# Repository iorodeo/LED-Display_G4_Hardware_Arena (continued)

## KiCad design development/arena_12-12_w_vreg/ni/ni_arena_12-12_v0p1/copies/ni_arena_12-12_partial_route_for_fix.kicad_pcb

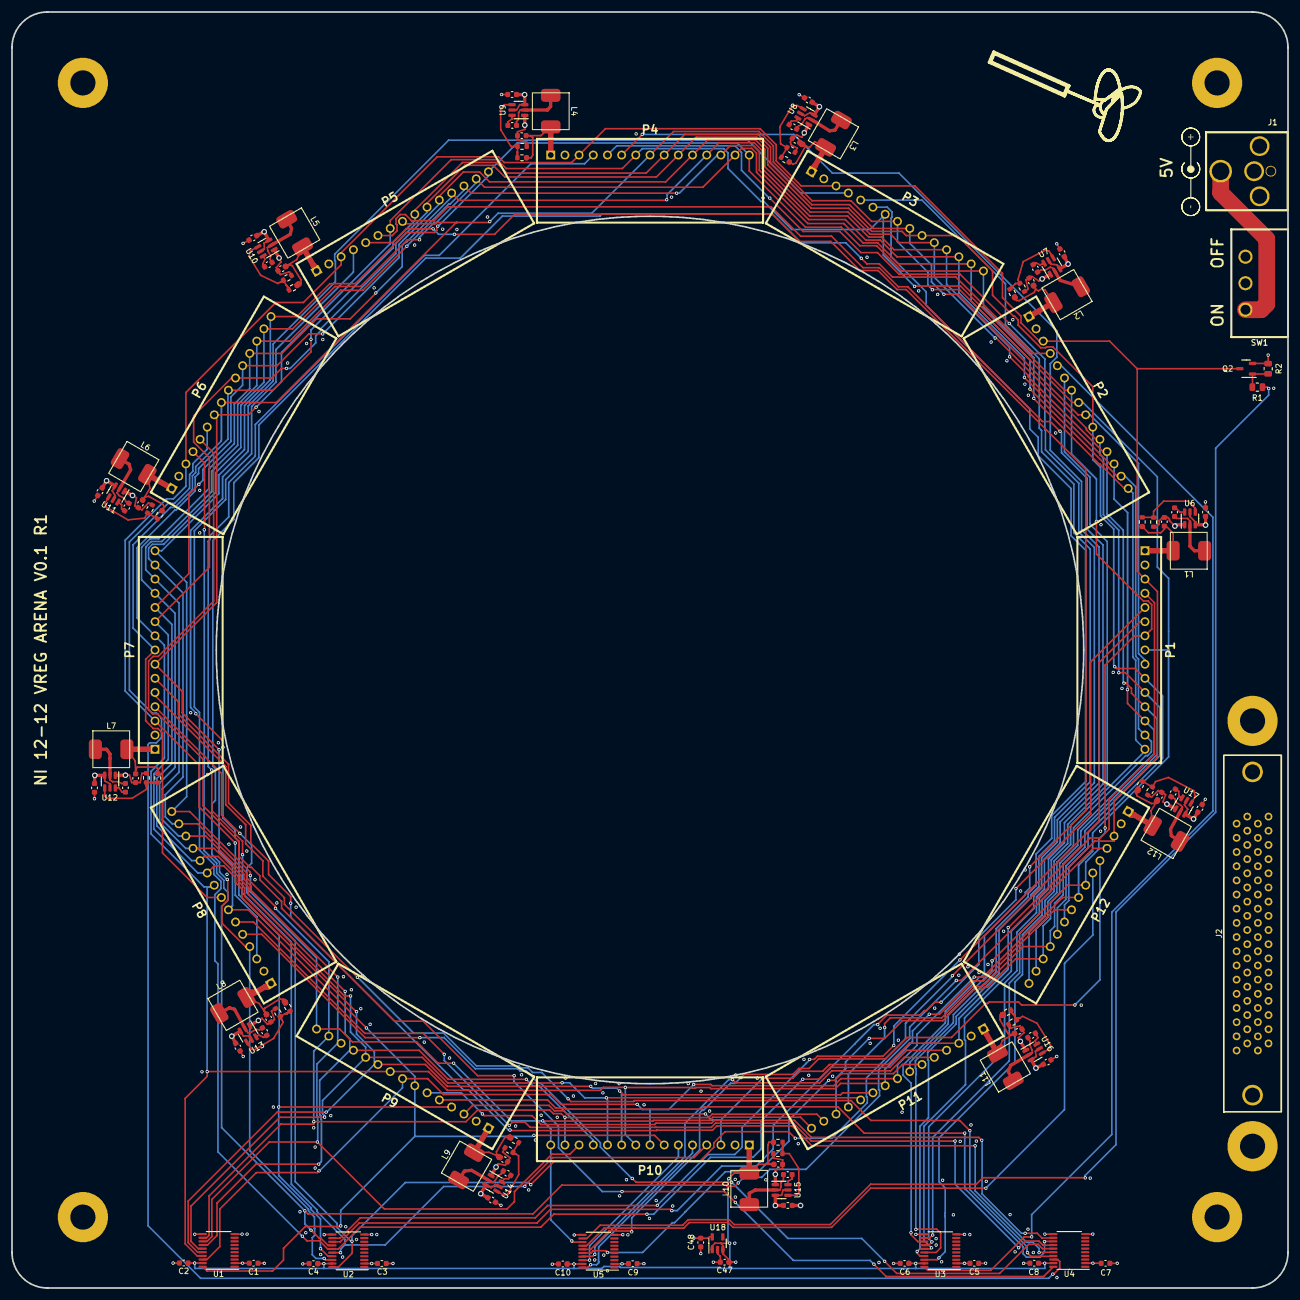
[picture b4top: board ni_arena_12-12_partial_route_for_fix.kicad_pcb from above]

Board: 6 copper layers, 228.6 x 228.6 mm, 126 parts (0 on the bottom side), 134 nets.

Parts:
C1, C2, C3, C4, C5, C6, C7, C8, C9, C10: 0.1uF; C_0603_1608Metric
C11, C14, C17, C20, C23, C26, C29, C32, C35, C38, C41, C44, C47, C48: 10uF; C_0603_1608Metric
C12, C15, C18, C21, C24, C27, C30, C33, C36, C39, C42, C45: 100nF; C_0603_1608Metric
C13, C16, C19, C22, C25, C28, C31, C34, C37, C40, C43, C46: 22uF; C_0603_1608Metric
H1, H2, H3, H4, H5, H6: MountingHole_Pad; MountingHole_4.5mm_Pad
J1: Barrel_Jack; DCJACK_2PIN_HIGHCURRENT
J2: NI_TE_68pos; TE_CONN_DSUB_VERT_68
L1, L2, L3, L4, L5, L6, L7, L8, L9, L10, L11, L12: 3.3uH; CYA0650_3P3UH
P1, P2, P3, P4, P5, P6, P7, P8, P9, P10, P11, P12: CONN15; HEADER_TOP
Q2: MOSFET_NCHAN; SOT-23-3
R1: 200; R_0805_2012Metric
R2: 20k; R_0805_2012Metric
R3, R5, R7, R9, R11, R13, R15, R17, R19, R21, R23, R25: 56.2k; R_0603_1608Metric
R4, R6, R8, R10, R12, R14, R16, R18, R20, R22, R24, R26: 10k; R_0603_1608Metric
SW1: SW_SPDT; slide_switch
U1, U2, U3, U4, U5: TXB0108PW; TSSOP-20_4.4x6.5mm_P0.65mm
U6, U7, U8, U9, U10, U11, U12, U13, U14, U15, U16, U17: TPS564201DDC; SOT-23-6
U18: AP2112K-3.3; SOT-23-5

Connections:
+3.3V: C1.1, C3.1, C5.1, C7.1, C9.1, C48.1, U1.2 (VCCA), U1.10 (OE), U2.2 (VCCA), U2.10 (OE), U3.2 (VCCA), U3.10 (OE), U4.2 (VCCA), U4.10 (OE), U5.2 (VCCA), U5.10 (OE), U18.5 (VOUT)
/Level Shifters/PAN3V.CS_00: J2.35, U1.1 (A1)
/Level Shifters/PAN3V.CS_01: J2.36, U1.3 (A2)
/Level Shifters/PAN3V.CS_02: J2.37, U1.4 (A3)
/Level Shifters/PAN3V.CS_03: J2.38, U1.5 (A4)
/Level Shifters/PAN3V.CS_04: J2.39, U1.6 (A5)
/Level Shifters/PAN3V.CS_05: J2.40, U1.7 (A6)
/Level Shifters/PAN3V.CS_06: J2.41, U1.8 (A7)
/Level Shifters/PAN3V.CS_07: J2.42, U1.9 (A8)
/Level Shifters/PAN3V.EXT_INT: J2.68, U5.8 (A7)
/Level Shifters/PAN3V.MISO_00: J2.50, U2.9 (A8)
/Level Shifters/PAN3V.MISO_01: J2.52, U3.3 (A2)
/Level Shifters/PAN3V.MISO_02: J2.54, U3.5 (A4)
/Level Shifters/PAN3V.MISO_03: J2.56, U3.7 (A6)
/Level Shifters/PAN3V.MISO_04: J2.58, U3.9 (A8)
/Level Shifters/PAN3V.MISO_05: J2.60, U4.3 (A2)
/Level Shifters/PAN3V.MISO_06: J2.62, U4.5 (A4)
/Level Shifters/PAN3V.MISO_07: J2.63, U4.7 (A6)
/Level Shifters/PAN3V.MISO_08: J2.64, U4.9 (A8)
/Level Shifters/PAN3V.MISO_09: J2.65, U5.3 (A2)
/Level Shifters/PAN3V.MISO_10: J2.66, U5.5 (A4)
/Level Shifters/PAN3V.MISO_11: J2.67, U5.7 (A6)
/Level Shifters/PAN3V.MOSI_00: J2.49, U2.8 (A7)
/Level Shifters/PAN3V.MOSI_01: J2.51, U3.1 (A1)
/Level Shifters/PAN3V.MOSI_02: J2.53, U3.4 (A3)
/Level Shifters/PAN3V.MOSI_03: J2.55, U3.6 (A5)
/Level Shifters/PAN3V.MOSI_04: J2.57, U3.8 (A7)
/Level Shifters/PAN3V.MOSI_05: J2.59, U4.1 (A1)
/Level Shifters/PAN3V.MOSI_06: J2.61, U4.4 (A3)
/Level Shifters/PAN3V.MOSI_07: J2.29, U4.6 (A5)
/Level Shifters/PAN3V.MOSI_08: J2.30, U4.8 (A7)
/Level Shifters/PAN3V.MOSI_09: J2.31, U5.1 (A1)
/Level Shifters/PAN3V.MOSI_10: J2.32, U5.4 (A3)
/Level Shifters/PAN3V.MOSI_11: J2.33, U5.6 (A5)
/Level Shifters/PAN3V.RESET: J2.34, U5.9 (A8)
/Level Shifters/PAN3V.SCK_00: J2.43, U2.1 (A1)
/Level Shifters/PAN3V.SCK_01: J2.44, U2.3 (A2)
/Level Shifters/PAN3V.SCK_02: J2.45, U2.4 (A3)
/Level Shifters/PAN3V.SCK_03: J2.46, U2.5 (A4)
/Level Shifters/PAN3V.SCK_04: J2.47, U2.6 (A5)
/Level Shifters/PAN3V.SCK_05: J2.48, U2.7 (A6)
/Level Shifters/PAN5V.CS_00: P1.7, P2.7, P3.7, P4.7, P5.7, P6.7, P7.7, P8.7, P9.7, P10.7, P11.7, P12.7, U1.20 (B1)
/Level Shifters/PAN5V.CS_01: P1.8, P2.8, P3.8, P4.8, P5.8, P6.8, P7.8, P8.8, P9.8, P10.8, P11.8, P12.8, U1.18 (B2)
/Level Shifters/PAN5V.CS_02: P1.9, P2.9, P3.9, P4.9, P5.9, P6.9, P7.9, P8.9, P9.9, P10.9, P11.9, P12.9, U1.17 (B3)
/Level Shifters/PAN5V.CS_03: P1.10, P2.10, P3.10, P4.10, P5.10, P6.10, P7.10, P8.10, P9.10, P10.10, P11.10, P12.10, U1.16 (B4)
/Level Shifters/PAN5V.CS_04: P1.11, P2.11, P3.11, P4.11, P5.11, P6.11, P7.11, P8.11, P9.11, P10.11, P11.11, P12.11, U1.15 (B5)
/Level Shifters/PAN5V.CS_05: P1.12, P2.12, P3.12, P4.12, P5.12, P6.12, P7.12, P8.12, P9.12, P10.12, P11.12, P12.12, U1.14 (B6)
/Level Shifters/PAN5V.CS_06: P1.13, P2.13, P3.13, P4.13, P5.13, P6.13, P7.13, P8.13, P9.13, P10.13, P11.13, P12.13, U1.13 (B7)
/Level Shifters/PAN5V.CS_07: P1.14, P2.14, P3.14, P4.14, P5.14, P6.14, P7.14, P8.14, P9.14, P10.14, P11.14, P12.14, U1.12 (B8)
/Level Shifters/PAN5V.EXT_INT: P1.15, P2.15, P3.15, P4.15, P5.15, P6.15, P7.15, P8.15, P9.15, P10.15, P11.15, P12.15, U5.13 (B7)
/Level Shifters/PAN5V.MISO_00: P1.6, U2.12 (B8)
/Level Shifters/PAN5V.MISO_01: P2.6, U3.18 (B2)
/Level Shifters/PAN5V.MISO_02: P3.6, U3.16 (B4)
/Level Shifters/PAN5V.MISO_03: P4.6, U3.14 (B6)
/Level Shifters/PAN5V.MISO_04: P5.6, U3.12 (B8)
/Level Shifters/PAN5V.MISO_05: P6.6, U4.18 (B2)
/Level Shifters/PAN5V.MISO_06: P7.6, U4.16 (B4)
/Level Shifters/PAN5V.MISO_07: P8.6, U4.14 (B6)
/Level Shifters/PAN5V.MISO_08: P9.6, U4.12 (B8)
/Level Shifters/PAN5V.MISO_09: P10.6, U5.18 (B2)
/Level Shifters/PAN5V.MISO_10: P11.6, U5.16 (B4)
/Level Shifters/PAN5V.MISO_11: P12.6, U5.14 (B6)
/Level Shifters/PAN5V.MOSI_00: P1.5, U2.13 (B7)
/Level Shifters/PAN5V.MOSI_01: P2.5, U3.20 (B1)
/Level Shifters/PAN5V.MOSI_02: P3.5, U3.17 (B3)
/Level Shifters/PAN5V.MOSI_03: P4.5, U3.15 (B5)
/Level Shifters/PAN5V.MOSI_04: P5.5, U3.13 (B7)
/Level Shifters/PAN5V.MOSI_05: P6.5, U4.20 (B1)
/Level Shifters/PAN5V.MOSI_06: P7.5, U4.17 (B3)
/Level Shifters/PAN5V.MOSI_07: P8.5, U4.15 (B5)
/Level Shifters/PAN5V.MOSI_08: P9.5, U4.13 (B7)
/Level Shifters/PAN5V.MOSI_09: P10.5, U5.20 (B1)
/Level Shifters/PAN5V.MOSI_10: P11.5, U5.17 (B3)
/Level Shifters/PAN5V.MOSI_11: P12.5, U5.15 (B5)
/Level Shifters/PAN5V.RESET: R1.2, U5.12 (B8)
/Level Shifters/PAN5V.SCK_00: P1.4, P7.4, U2.20 (B1)
/Level Shifters/PAN5V.SCK_01: P2.4, P8.4, U2.18 (B2)
/Level Shifters/PAN5V.SCK_02: P3.4, P9.4, U2.17 (B3)
/Level Shifters/PAN5V.SCK_03: P4.4, P10.4, U2.16 (B4)
/Level Shifters/PAN5V.SCK_04: P5.4, P11.4, U2.15 (B5)
/Level Shifters/PAN5V.SCK_05: P6.4, P12.4, U2.14 (B6)
/Level Shifters/POW.5V_HDR_1: C13.2, L1.2, P1.1, R3.1
/Level Shifters/POW.5V_HDR_2: C16.2, L2.2, P2.1, R5.1
/Level Shifters/POW.5V_HDR_3: C19.2, L3.2, P3.1, R7.1
/Level Shifters/POW.5V_HDR_4: C22.2, L4.2, P4.1, R9.1
/Level Shifters/POW.5V_HDR_5: C25.2, L5.2, P5.1, R11.1
/Level Shifters/POW.5V_HDR_6: C28.2, L6.2, P6.1, R13.1
/Level Shifters/POW.5V_HDR_7: C31.2, L7.2, P7.1, R15.1
/Level Shifters/POW.5V_HDR_8: C34.2, L8.2, P8.1, R17.1
/Level Shifters/POW.5V_HDR_9: C37.2, L9.2, P9.1, R19.1
/Level Shifters/POW.5V_HDR_10: C2.1, C4.1, C6.1, C8.1, C10.1, C40.2, C47.1, L10.2, P10.1, R21.1, U1.19 (VCCB), U2.19 (VCCB), U3.19 (VCCB), U4.19 (VCCB), U5.19 (VCCB), U18.1 (VIN), U18.3 (EN)
/Level Shifters/POW.5V_HDR_11: C43.2, L11.2, P11.1, R23.1
/Level Shifters/POW.5V_HDR_12: C46.2, L12.2, P12.1, R25.1
/Panel Headers/RESET: P1.3, P2.3, P3.3, P4.3, P5.3, P6.3, P7.3, P8.3, P9.3, P10.3, P11.3, P12.3, Q2.3 (D)
/Power & Voltage Regulators/SW_VCC: J1.1, SW1.1 (A)
GND: C1.2, C2.2, C3.2, C4.2, C5.2, C6.2, C7.2, C8.2, C9.2, C10.2, C11.2, C13.1, C14.2, C16.1, C17.2, C19.1, C20.2, C22.1, C23.2, C25.1, C26.2, C28.1, C29.2, C31.1, C32.2, C34.1, C35.2, C37.1, C38.2, C40.1, C41.2, C43.1, C44.2, C46.1, C47.2, C48.2, H1.1, H2.1, H3.1, H4.1, H5.1, H6.1, J1.2, J2.1, J2.2, J2.3, J2.69 (GND), J2.70 (GND), P1.2, P2.2, P3.2, P4.2, P5.2, P6.2, P7.2, P8.2, P9.2, P10.2, P11.2, P12.2, Q2.2 (S), R2.1, R4.2, R6.2, R8.2, R10.2, R12.2, R14.2, R16.2, R18.2, R20.2, R22.2, R24.2, R26.2, SW1.3 (C), U1.11 (GND), U2.11 (GND), U3.11 (GND), U4.11 (GND), U5.11 (GND), U6.1 (GND), U7.1 (GND), U8.1 (GND), U9.1 (GND), U10.1 (GND), U11.1 (GND), U12.1 (GND), U13.1 (GND), U14.1 (GND), U15.1 (GND), U16.1 (GND), U17.1 (GND), U18.2 (GND)
unnamed: Q2.1 (G), R1.1, R2.2
unnamed: C12.2, L1.1, U6.2 (SW)
unnamed: C12.1, U6.6 (VBST)
unnamed: R3.2, R4.1, U6.4 (VFB)
unnamed: C15.2, L2.1, U7.2 (SW)
unnamed: C15.1, U7.6 (VBST)
unnamed: R5.2, R6.1, U7.4 (VFB)
unnamed: C18.2, L3.1, U8.2 (SW)
unnamed: C18.1, U8.6 (VBST)
unnamed: R7.2, R8.1, U8.4 (VFB)
unnamed: C21.2, L4.1, U9.2 (SW)
unnamed: C21.1, U9.6 (VBST)
unnamed: R9.2, R10.1, U9.4 (VFB)
unnamed: C24.2, L5.1, U10.2 (SW)
unnamed: C24.1, U10.6 (VBST)
unnamed: R11.2, R12.1, U10.4 (VFB)
unnamed: C27.2, L6.1, U11.2 (SW)
unnamed: C27.1, U11.6 (VBST)
unnamed: R13.2, R14.1, U11.4 (VFB)
unnamed: C30.2, L7.1, U12.2 (SW)
unnamed: C30.1, U12.6 (VBST)
unnamed: R15.2, R16.1, U12.4 (VFB)
unnamed: C33.2, L8.1, U13.2 (SW)
unnamed: C33.1, U13.6 (VBST)
unnamed: R17.2, R18.1, U13.4 (VFB)
unnamed: C36.2, L9.1, U14.2 (SW)
unnamed: C36.1, U14.6 (VBST)
unnamed: R19.2, R20.1, U14.4 (VFB)
unnamed: C39.2, L10.1, U15.2 (SW)
unnamed: C39.1, U15.6 (VBST)
unnamed: R21.2, R22.1, U15.4 (VFB)
unnamed: C42.2, L11.1, U16.2 (SW)
unnamed: C42.1, U16.6 (VBST)
unnamed: R23.2, R24.1, U16.4 (VFB)
unnamed: C45.2, L12.1, U17.2 (SW)
unnamed: C45.1, U17.6 (VBST)
unnamed: R25.2, R26.1, U17.4 (VFB)
VCC: C11.1, C14.1, C17.1, C20.1, C23.1, C26.1, C29.1, C32.1, C35.1, C38.1, C41.1, C44.1, SW1.2 (B), U6.3 (VIN), U6.5 (EN), U7.3 (VIN), U7.5 (EN), U8.3 (VIN), U8.5 (EN), U9.3 (VIN), U9.5 (EN), U10.3 (VIN), U10.5 (EN), U11.3 (VIN), U11.5 (EN), U12.3 (VIN), U12.5 (EN), U13.3 (VIN), U13.5 (EN), U14.3 (VIN), U14.5 (EN), U15.3 (VIN), U15.5 (EN), U16.3 (VIN), U16.5 (EN), U17.3 (VIN), U17.5 (EN)
